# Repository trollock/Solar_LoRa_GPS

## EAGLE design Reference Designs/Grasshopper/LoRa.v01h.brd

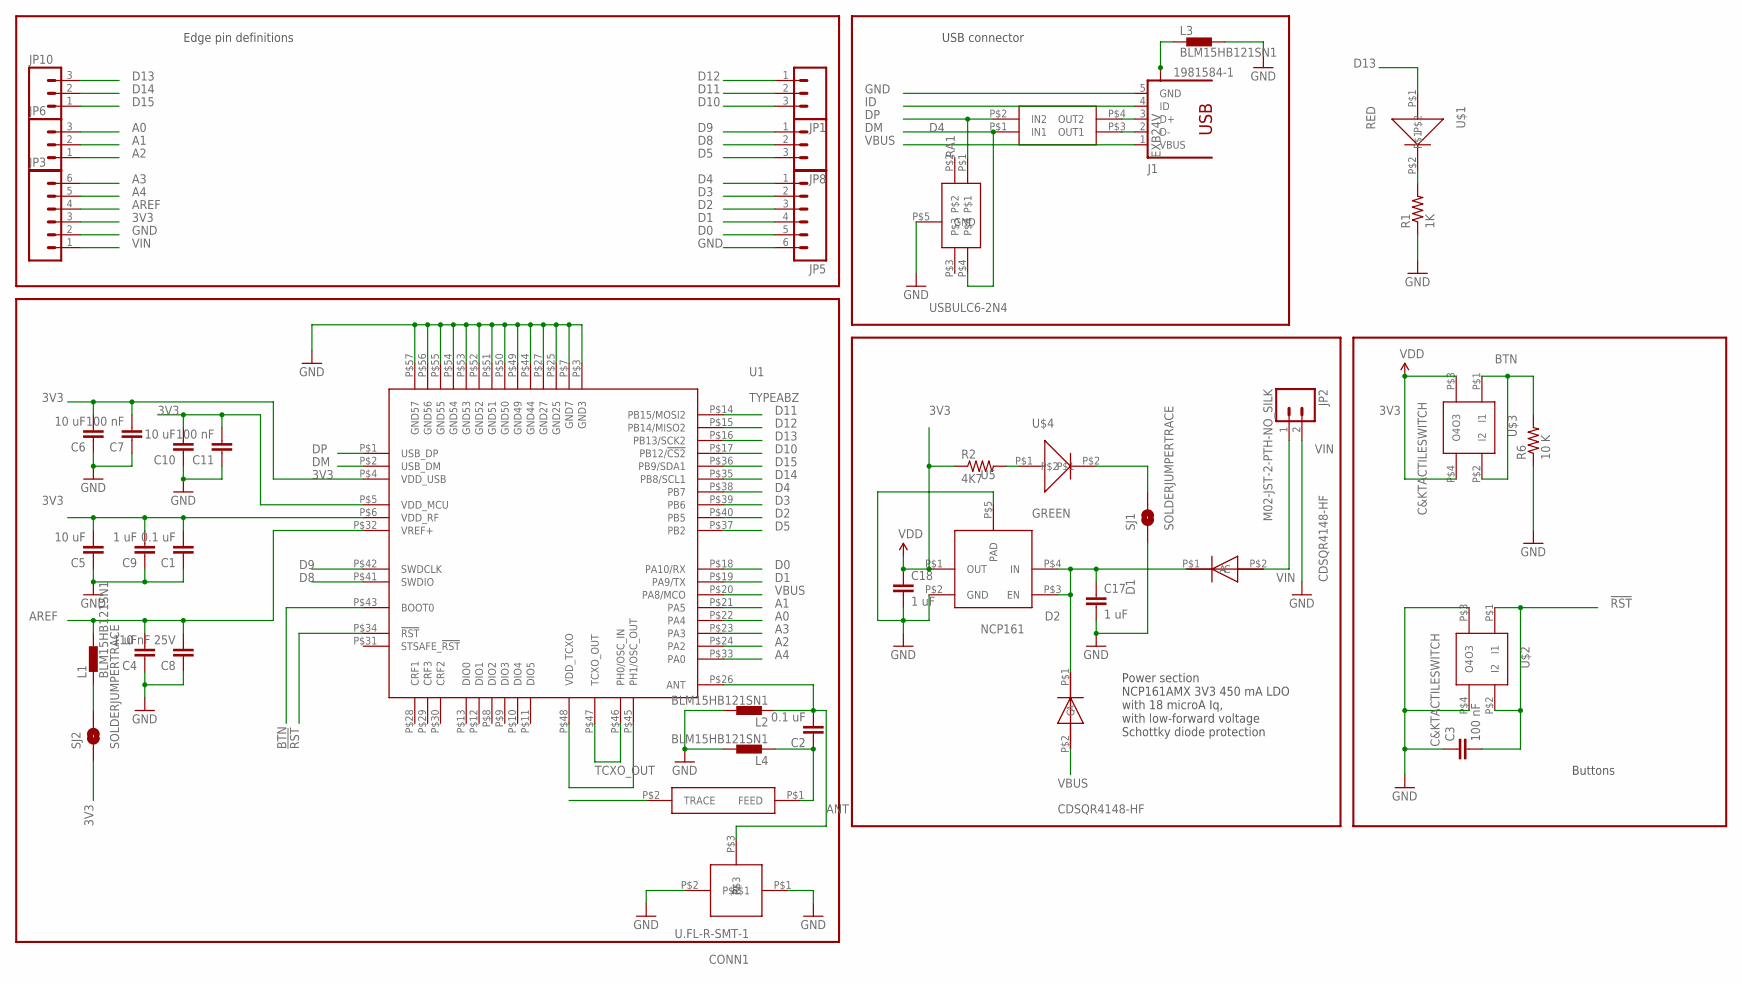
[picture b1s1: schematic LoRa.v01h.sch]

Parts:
C1, C2: 0.1 uF; 0402-CAP
C3, C7, C11: 100 nF; 0402-CAP
C4, C9, C17, C18: 1 uF; 0402-CAP
C5, C6, C10: 10 uF; 0402-CAP
C8: 10 nF 25V; 0402-CAP
CONN1: U.FL-R-SMT-1
D1, D2: CDSQR4148-HF
D4: USBULC6-2N4
J1: 1981584-1; MPN ZX62-AB-5PA(11)
JP1, JP6, JP8, JP10: M031X03_NO_SILK; 1X03_NO_SILK
JP2: M02-JST-2-PTH-NO_SILK; JST-2-PTH-NS
JP3, JP5: M06NO_SILK; 1X06_NO_SILK
L1, L2, L3, L4: BLM15HB121SN1; 0402
R1: 1K; 0402-RES
R2: 4K7; 0402-RES
R6: 10 K; 0402-RES
RA1: EXB24V
SJ1, SJ2: SOLDERJUMPERTRACE; SJ_2S-TRACE
U1: TYPEABZ
U5: NCP161
U$1: RED; 0402LED
U$2, U$3: C&KTACTILESWITCH
U$4: GREEN; 0402LED
U$5: JOHANSON0900AT43A0070

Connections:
3V3: C1.2, C5.2, C6.2, C7.2, C9.2, C10.2, C11.2, C18.1, JP3.3, R2.1, SJ2.1, U1.P$4 (VDD_USB), U1.P$5 (VDD_MCU), U1.P$6 (VDD_RF), U5.P$1 (OUT), U$3.P$3 (O3), U$3.P$4 (O4)
!RST: C3.2, U1.P$34 (!RST), U$2.P$1 (I1), U$2.P$2 (I2)
A0: JP6.3, U1.P$22 (PA4)
A1: JP6.2, U1.P$21 (PA5)
A2: JP6.1, U1.P$24 (PA2)
A3: JP3.6, U1.P$23 (PA3)
A4: JP3.5, U1.P$33 (PA0)
ANT: C2.1, L4.1, U$5.P$1 (FEED)
AREF: C4.2, C8.2, JP3.4, L1.2, U1.P$32 (VREF+)
BTN: R6.2, U1.P$43 (BOOT0), U$3.P$1 (I1), U$3.P$2 (I2)
D0: JP5.5, U1.P$18 (PA10/RX)
D1: JP5.4, U1.P$19 (PA9/TX)
D2: JP5.3, U1.P$40 (PB5)
D3: JP5.2, U1.P$39 (PB6)
D4: JP5.1, U1.P$38 (PB7)
D5: JP8.3, U1.P$37 (PB2)
D8: JP8.2, U1.P$41 (SWDIO)
D9: JP8.1, U1.P$42 (SWDCLK)
D10: JP1.3, U1.P$17 (PB12/!CS2)
D11: JP1.2, U1.P$14 (PB15/MOSI2)
D12: JP1.1, U1.P$15 (PB14/MISO2)
D13: JP10.3, U1.P$16 (PB13/SCK2), U$1.P$1
D14: JP10.2, U1.P$35 (PB8/SCL1)
D15: JP10.1, U1.P$36 (PB9/SDA1)
DM: D4.P$4, RA1.P$1 (IN1), U1.P$2 (USB_DM)
DP: D4.P$1, RA1.P$2 (IN2), U1.P$1 (USB_DP)
GND: C1.1, C3.1, C4.1, C5.1, C6.1, C7.1, C8.1, C9.1, C10.1, C11.1, C17.2, C18.2, CONN1.P$1, CONN1.P$2, D4.P$5 (GND), J1.5 (GND), JP2.2, JP3.2, JP5.6, L2.2, L3.2, L4.2, R1.1, R6.1, SJ1.1, U1.P$3 (GND3), U1.P$7 (GND7), U1.P$25 (GND25), U1.P$27 (GND27), U1.P$44 (GND44), U1.P$49 (GND49), U1.P$50 (GND50), U1.P$51 (GND51), U1.P$52 (GND52), U1.P$53 (GND53), U1.P$54 (GND54), U1.P$55 (GND55), U1.P$56 (GND56), U1.P$57 (GND57), U5.P$2 (GND), U5.P$5 (PAD), U$2.P$3 (O3), U$2.P$4 (O4)
ID: J1.4 (ID)
unnamed: R1.2, U$1.P$2
unnamed: L1.1, SJ2.2
unnamed: U1.P$45 (PH1/OSC_OUT), U1.P$48 (VDD_TCXO)
unnamed: SJ1.2, U$4.P$2
unnamed: J1.3 (D+), RA1.P$4 (OUT2)
unnamed: C2.2, CONN1.P$3, L2.1, U1.P$26 (ANT)
unnamed: J1.2 (D-), RA1.P$3 (OUT1)
unnamed: R2.2, U$4.P$1
unnamed: C17.1, D1.P$1 (C), D2.P$1 (C), U5.P$3 (EN), U5.P$4 (IN)
TCXO_OUT: U1.P$46 (PH0/OSC_IN), U1.P$47 (TCXO_OUT)
USB_SHIELD: J1.S1, J1.S2, J1.S3, J1.S4, L3.1
VBUS: D2.P$2 (A), J1.1 (VBUS), U1.P$20 (PA8/MCO)
VIN: D1.P$2 (A), JP2.1, JP3.1

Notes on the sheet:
Edge pin definitions
USB connector
Power section NCP161AMX 3V3 450 mA LDO with 18 microA Iq, with low-forward voltage Schottky diode protection
Buttons

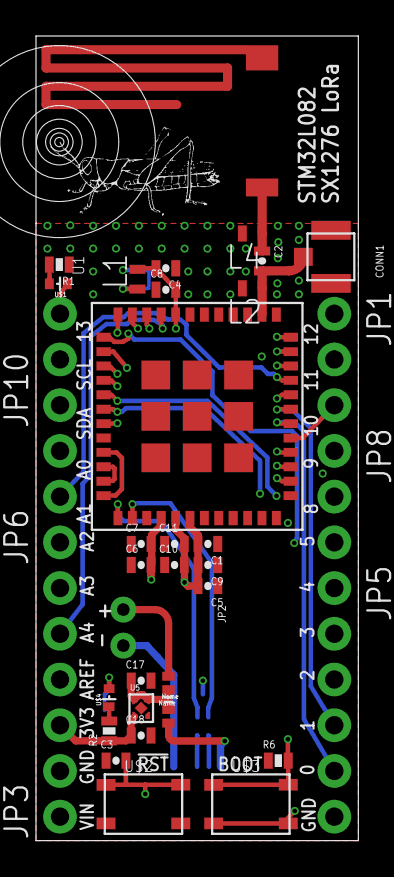
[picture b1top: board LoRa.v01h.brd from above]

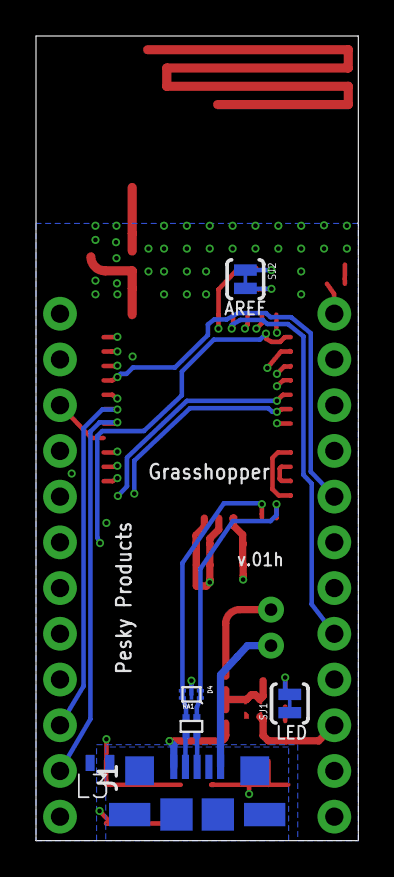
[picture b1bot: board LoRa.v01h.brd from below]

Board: 4 copper layers, 17.9 x 44.7 mm, 43 parts (6 on the bottom side), 40 nets.

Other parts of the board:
U$6: GRASSHOPPER

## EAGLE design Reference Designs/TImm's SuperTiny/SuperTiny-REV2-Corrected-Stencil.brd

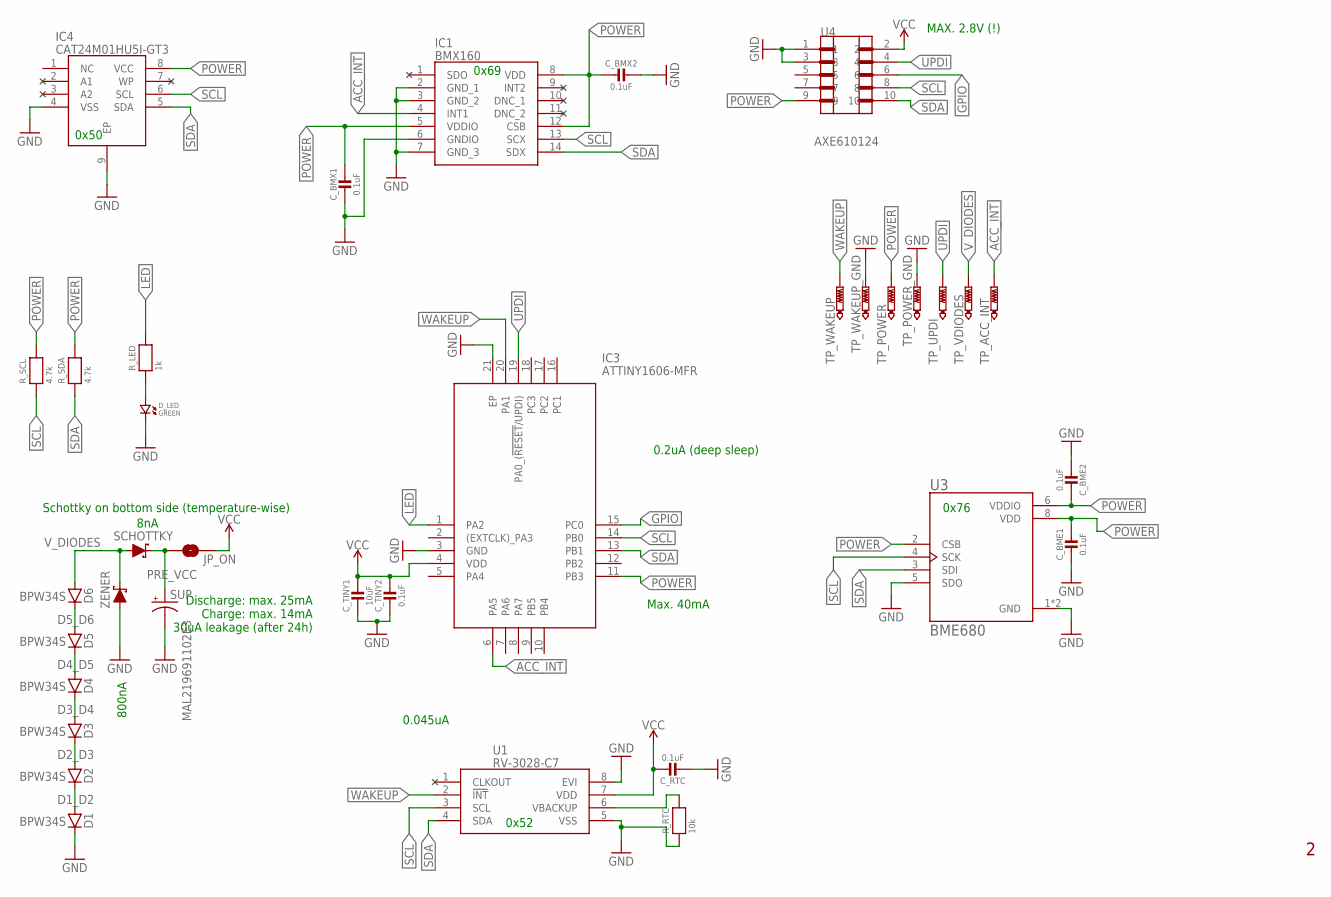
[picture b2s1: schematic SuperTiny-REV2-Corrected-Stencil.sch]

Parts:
C_BME1, C_BME2: 0.1uF; MICROBUILDER__0402MP
C_BMX1, C_BMX2: 0.1uF; MICROBUILDER__0402MP
C_RTC: 0.1uF; MICROBUILDER__0402MP
C_TINY1: 10uF; MICROBUILDER__0402MP
C_TINY2: 0.1uF; MICROBUILDER__0402MP
D1, D2, D3, D4, D5, D6: BPW34S
D_LED: GREEN; CMONR_STANDARDPARTS_0402.LED
IC1: BMX160; PQFN50P300X250X88-14N
IC3: ATTINY1606-MFR; QFN40P300X300X90-21N
IC4: CAT24M01HU5I-GT3; SON50P300X200X55-9N
JP_ON: JUMPER-SMT_2_NO_NO-SILK; SMT-JUMPER_2_NO_NO-SILK
R_LED: 1k; MICROBUILDER__0402MP
R_RTC: 10k; MICROBUILDER__0402MP
R_SCL: 4.7k; MICROBUILDER__0402MP
R_SDA: 4.7k; MICROBUILDER__0402MP
SCHOTTKY: NSR0140P2T5G
SUP: MAL219691102E3
TP_ACC_INT: PTR1TP06SQ; TP06SQ
TP_POWER: PTR1TP06SQ; TP06SQ
TP_POWER_GND: PTR1TP06SQ; TP06SQ
TP_UPDI: PTR1TP06SQ; TP06SQ
TP_VDIODES: PTR1TP06SQ; TP06SQ
TP_WAKEUP: PTR1TP06SQ; TP06SQ
TP_WAKEUP_GND: PTR1TP06SQ; TP06SQ
U1: RV-3028-C7; RV3028C7
U3: BME680; PSON80P300X300X100-8N
U4: AXE610124
ZENER: MMSZ4683T1G

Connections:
ACC_INT: IC1.4 (INT1), IC3.6 (PA5), TP_ACC_INT.TP
D1_D2: D1.PLUS, D2.MINUS
D2_D3: D2.PLUS, D3.MINUS
D3_D4: D3.PLUS, D4.MINUS
D4_D5: D4.PLUS, D5.MINUS
D5_D6: D5.PLUS, D6.MINUS
GND: C_BME1.2, C_BME2.2, C_BMX1.2, C_BMX2.1, C_RTC.2, C_TINY1.2, C_TINY2.2, D1.MINUS, D_LED.P$2 (2), IC1.2 (GND_1), IC1.3 (GND_2), IC1.6 (GNDIO), IC1.7 (GND_3), IC3.3 (GND), IC3.21 (EP), IC4.4 (VSS), IC4.9 (EP), R_RTC.1, SUP.MINUS (-), TP_POWER_GND.TP, TP_WAKEUP_GND.TP, U1.5 (VSS), U1.8 (EVI), U3.1 (GND), U3.5 (SDO), U3.7 (GND), U4.1, U4.3, ZENER.P$1 (AN)
GPIO: IC3.15 (PC0), U4.6
LED: IC3.1 (PA2), R_LED.2
unnamed: R_RTC.2, U1.6 (VBACKUP)
unnamed: D_LED.P$1 (1), R_LED.1
POWER: C_BME1.1, C_BME2.1, C_BMX1.1, C_BMX2.2, IC1.5 (VDDIO), IC1.8 (VDD), IC1.12 (CSB), IC3.11 (PB3), IC4.8 (VCC), R_SCL.2, R_SDA.2, TP_POWER.TP, U3.2 (CSB), U3.6 (VDDIO), U3.8 (VDD), U4.9
PRE_VCC: JP_ON.1, SCHOTTKY.P$2 (CA), SUP.PLUS (+)
SCL: IC1.13 (SCX), IC3.14 (PB0), IC4.6 (SCL), R_SCL.1, U1.3 (SCL), U3.4 (SCK), U4.8
SDA: IC1.14 (SDX), IC3.13 (PB1), IC4.5 (SDA), R_SDA.1, U1.4 (SDA), U3.3 (SDI), U4.10
UPDI: IC3.19 (PA0_(!RESET!/UPDI)), TP_UPDI.TP, U4.4
VCC: C_RTC.1, C_TINY1.1, C_TINY2.1, IC3.4 (VDD), JP_ON.2, U1.7 (VDD), U4.2
V_DIODES: D6.PLUS, SCHOTTKY.P$1 (AN), TP_VDIODES.TP, ZENER.P$2 (CA)
WAKEUP: IC3.20 (PA1), TP_WAKEUP.TP, U1.2 (!INT)

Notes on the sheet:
Schottky on bottom side (temperature-wise)
MAX. 2.8V (!)
0.045uA
800nA
0x50
0x69
0x52
8nA
0x76
0.2uA (deep sleep)
Discharge: max. 25mA Charge: max. 14mA 30uA leakage (after 24h)
Max. 40mA

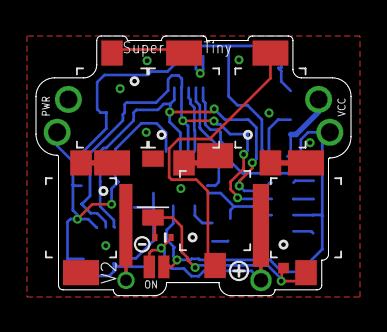
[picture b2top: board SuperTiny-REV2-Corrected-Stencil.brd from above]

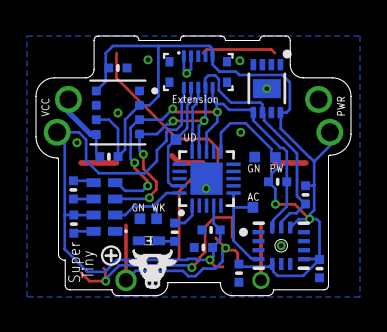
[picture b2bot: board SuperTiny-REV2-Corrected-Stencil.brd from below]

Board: 2 copper layers, 17.5 x 14.4 mm, 35 parts (24 on the bottom side), 19 nets.

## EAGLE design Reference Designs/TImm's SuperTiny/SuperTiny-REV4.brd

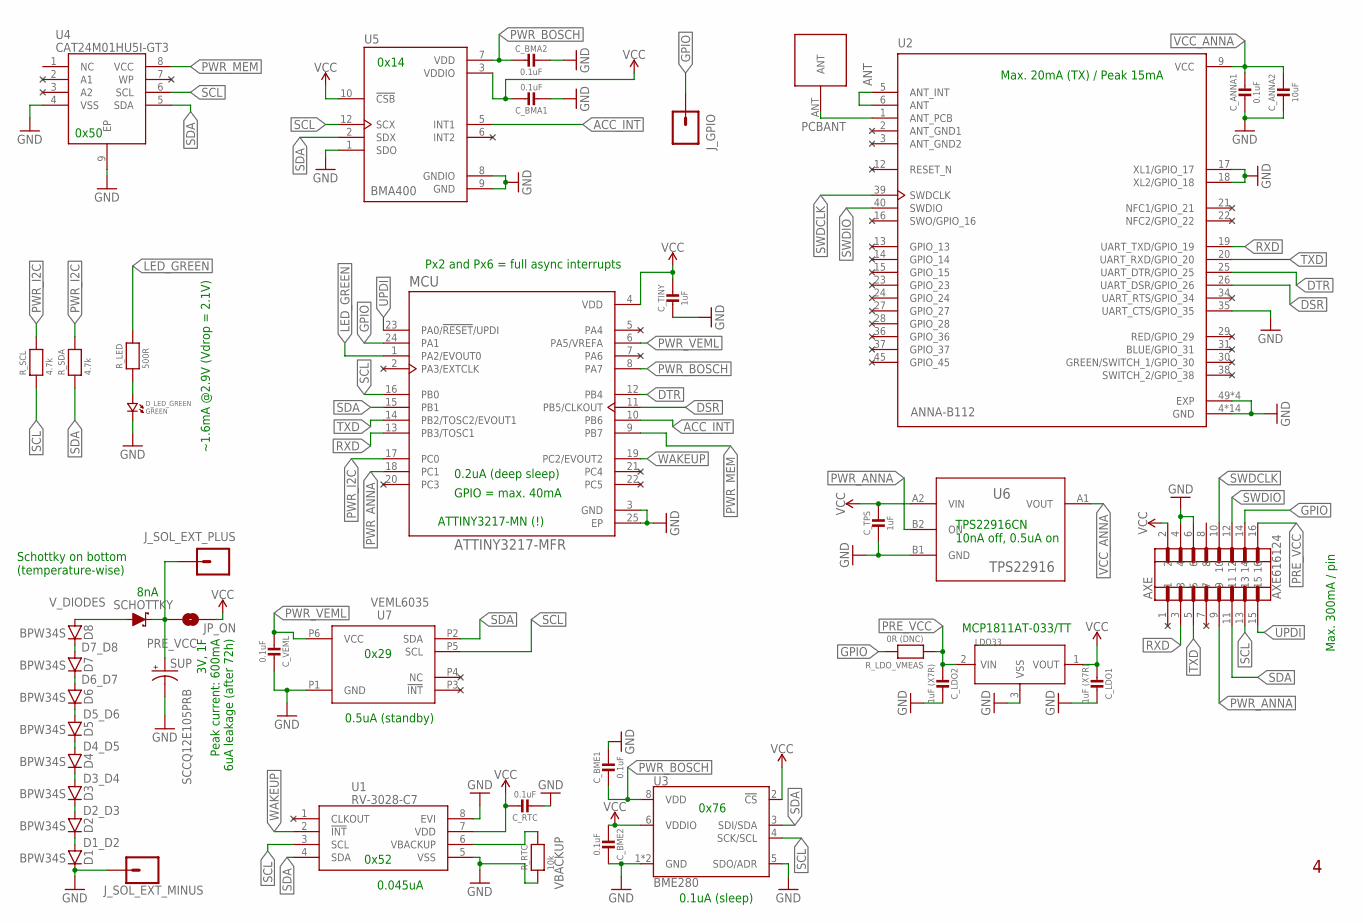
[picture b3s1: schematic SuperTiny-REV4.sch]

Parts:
AXE: AXE616124
C_ANNA1: 0.1uF; MICROBUILDER__0402MP
C_ANNA2: 10uF; MICROBUILDER__0402MP
C_BMA1, C_BMA2: 0.1uF; MICROBUILDER__0402MP
C_BME1, C_BME2: 0.1uF; MICROBUILDER__0402MP
C_LDO1, C_LDO2: 1uF (X7R); MICROBUILDER__0402MP
C_RTC: 0.1uF; MICROBUILDER__0402MP
C_TINY: 1uF; MICROBUILDER__0402MP
C_TPS: 1uF; MICROBUILDER__0402MP
C_VEML: 0.1uF; MICROBUILDER__0402MP
D1, D2, D3, D4, D5, D6, D7, D8: BPW34S
D_LED_GREEN: GREEN; CMONR_STANDARDPARTS_0402.LED
JP_ON: JUMPER-SMT_2_NO_NO-SILK; SMT-JUMPER_2_NO_NO-SILK
J_GPIO: CONN_01PTH_NO_SILK_SMALL; 1X01_SMALL
J_SOL_EXT_MINUS: CONN_01PTH_NO_SILK_SMALL; 1X01_SMALL
J_SOL_EXT_PLUS: CONN_01PTH_NO_SILK_SMALL; 1X01_SMALL
LDO33: MCP1812BT-018LB; SOT-23
MCU: ATTINY3217-MFR; QFN50P400X400X90-25N
R_LDO_VMEAS: 0R (DNC); MICROBUILDER__0402MP
R_LED: 500R; MICROBUILDER__0402MP
R_RTC: 10k; MICROBUILDER__0402MP
R_SCL: 4.7k; MICROBUILDER__0402MP
R_SDA: 4.7k; MICROBUILDER__0402MP
SCHOTTKY: NSR0140P2T5G
SUP: SCCQ12E105PRB
U1: RV-3028-C7; RV3028C7
U2: ANNA-B112; XCVR_ANNA-B112
U3: BME280; LGA-8-2.5X2.5
U4: CAT24M01HU5I-GT3; SON50P300X200X55-9N
U5: BMA400; XDCR_BMA400
U6: TPS22916
U7: VEML6035
U$4: ANNA-B112-PCB-ANTENNA

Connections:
ACC_INT: MCU.10 (PB6), U5.5 (INT1)
ANT: U2.5 (ANT_INT), U2.6 (ANT)
ANT_GND1: U2.2 (ANT_GND1)
ANT_GND2: U2.3 (ANT_GND2)
D1_D2: D1.PLUS, D2.MINUS
D2_D3: D2.PLUS, D3.MINUS
D3_D4: D3.PLUS, D4.MINUS
D4_D5: D4.PLUS, D5.MINUS
D5_D6: D5.PLUS, D6.MINUS
D6_D7: D6.PLUS, D7.MINUS
D7_D8: D7.PLUS, D8.MINUS
DSR: MCU.11 (PB5/CLKOUT), U2.26 (UART_DSR/GPIO_26)
DTR: MCU.12 (PB4), U2.25 (UART_DTR/GPIO_25)
GND: AXE.4, AXE.6, C_ANNA1.2, C_ANNA2.2, C_BMA1.2, C_BMA2.1, C_BME1.1, C_BME2.1, C_LDO1.1, C_LDO2.1, C_RTC.2, C_TINY.2, C_TPS.2, C_VEML.1, D1.MINUS, D_LED_GREEN.P$2 (2), J_SOL_EXT_MINUS.P$1, LDO33.3 (VSS), MCU.3 (GND), MCU.25 (EP), R_RTC.1, SUP.MINUS (-), U1.5 (VSS), U1.8 (EVI), U2.4 (GND), U2.7 (GND), U2.8 (GND), U2.10 (GND), U2.11 (GND), U2.17 (XL1/GPIO_17), U2.18 (XL2/GPIO_18), U2.32 (GND), U2.33 (GND), U2.35 (UART_CTS/GPIO_35), U2.41 (GND), U2.42 (GND), U2.43 (GND), U2.44 (GND), U2.46 (GND), U2.47 (GND), U2.48 (GND), U2.49 (EXP), U2.50 (EXP), U2.51 (EXP), U2.52 (EXP), U3.1 (GND), U3.5 (SDO/ADR), U3.7 (GND), U4.4 (VSS), U4.9 (EP), U5.1 (SDO), U5.8 (GNDIO), U5.9 (GND), U6.B1 (GND), U7.P1 (GND)
GPIO: AXE.14, J_GPIO.P$1, MCU.24 (PA1), R_LDO_VMEAS.2
LED_GREEN: MCU.1 (PA2/EVOUT0), R_LED.2
unnamed: D_LED_GREEN.P$1 (1), R_LED.1
PCBANT: U2.1 (ANT_PCB), U$4.ANT
PRE_VCC: AXE.16, C_LDO2.2, JP_ON.1, J_SOL_EXT_PLUS.P$1, LDO33.2 (VIN), R_LDO_VMEAS.1, SCHOTTKY.P$2 (CA), SUP.PLUS (+)
PWR_ANNA: AXE.9, MCU.18 (PC1), U6.B2 (ON)
PWR_BOSCH: C_BMA2.2, C_BME1.2, MCU.8 (PA7), U3.8 (VDD), U5.7 (VDD)
PWR_I2C: MCU.17 (PC0), R_SCL.2, R_SDA.2
PWR_MEM: MCU.9 (PB7), U4.8 (VCC)
PWR_VEML: C_VEML.2, MCU.6 (PA5/VREFA), U7.P6 (VCC)
RXD: AXE.3, MCU.13 (PB3/TOSC1), U2.19 (UART_TXD/GPIO_19)
SCL: AXE.13, MCU.16 (PB0), R_SCL.1, U1.3 (SCL), U3.4 (SCK/SCL), U4.6 (SCL), U5.12 (SCX), U7.P5 (SCL)
SDA: AXE.11, MCU.15 (PB1), R_SDA.1, U1.4 (SDA), U3.3 (SDI/SDA), U4.5 (SDA), U5.2 (SDX), U7.P2 (SDA)
SWDCLK: AXE.10, U2.39 (SWDCLK)
SWDIO: AXE.12, U2.40 (SWDIO)
TXD: AXE.5, MCU.14 (PB2/TOSC2/EVOUT1), U2.20 (UART_RXD/GPIO_20)
UPDI: AXE.15, MCU.23 (PA0/!RESET!/UPDI)
VBACKUP: R_RTC.2, U1.6 (VBACKUP)
VCC: AXE.2, C_BMA1.1, C_BME2.2, C_LDO1.2, C_RTC.1, C_TINY.1, C_TPS.1, JP_ON.2, LDO33.1 (VOUT), MCU.4 (VDD), U1.7 (VDD), U3.2 (!CS), U3.6 (VDDIO), U5.3 (VDDIO), U5.10 (!CSB), U6.A2 (VIN)
VCC_ANNA: C_ANNA1.1, C_ANNA2.1, U2.9 (VCC), U6.A1 (VOUT)
V_DIODES: D8.PLUS, SCHOTTKY.P$1 (AN)
WAKEUP: MCU.19 (PC2/EVOUT2), U1.2 (!INT)

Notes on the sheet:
Schottky on bottom (temperature-wise)
0.045uA
0x50
0x52
8nA
3V, 1F Peak current: 600mA 6uA leakage (after 72h)
Max. 20mA (TX) / Peak 15mA
~1.6mA @2.9V (Vdrop = 2.1V)
0x14
Max. 300mA / pin
0x76
0.1uA (sleep)
0.2uA (deep sleep)
GPIO = max. 40mA
Px2 and Px6 = full async interrupts
0x29
0.5uA (standby)
MCP1811AT-033/TT
TPS22916CN 10nA off, 0.5uA on
ATTINY3217-MN (!)

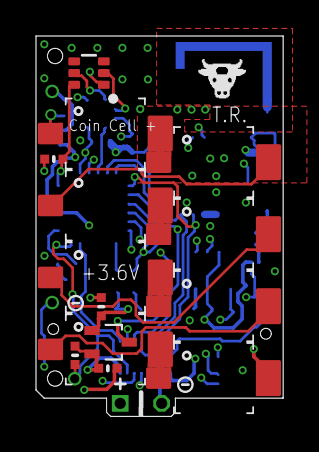
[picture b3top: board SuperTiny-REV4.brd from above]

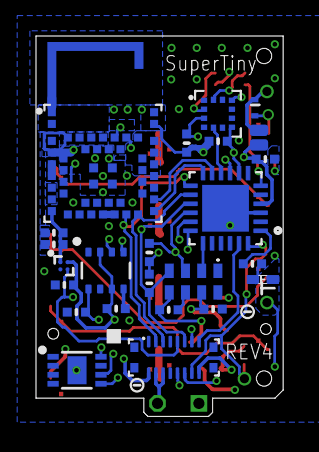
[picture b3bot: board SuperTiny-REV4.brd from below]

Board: 4 copper layers, 13.7 x 21.1 mm, 43 parts (25 on the bottom side), 34 nets.

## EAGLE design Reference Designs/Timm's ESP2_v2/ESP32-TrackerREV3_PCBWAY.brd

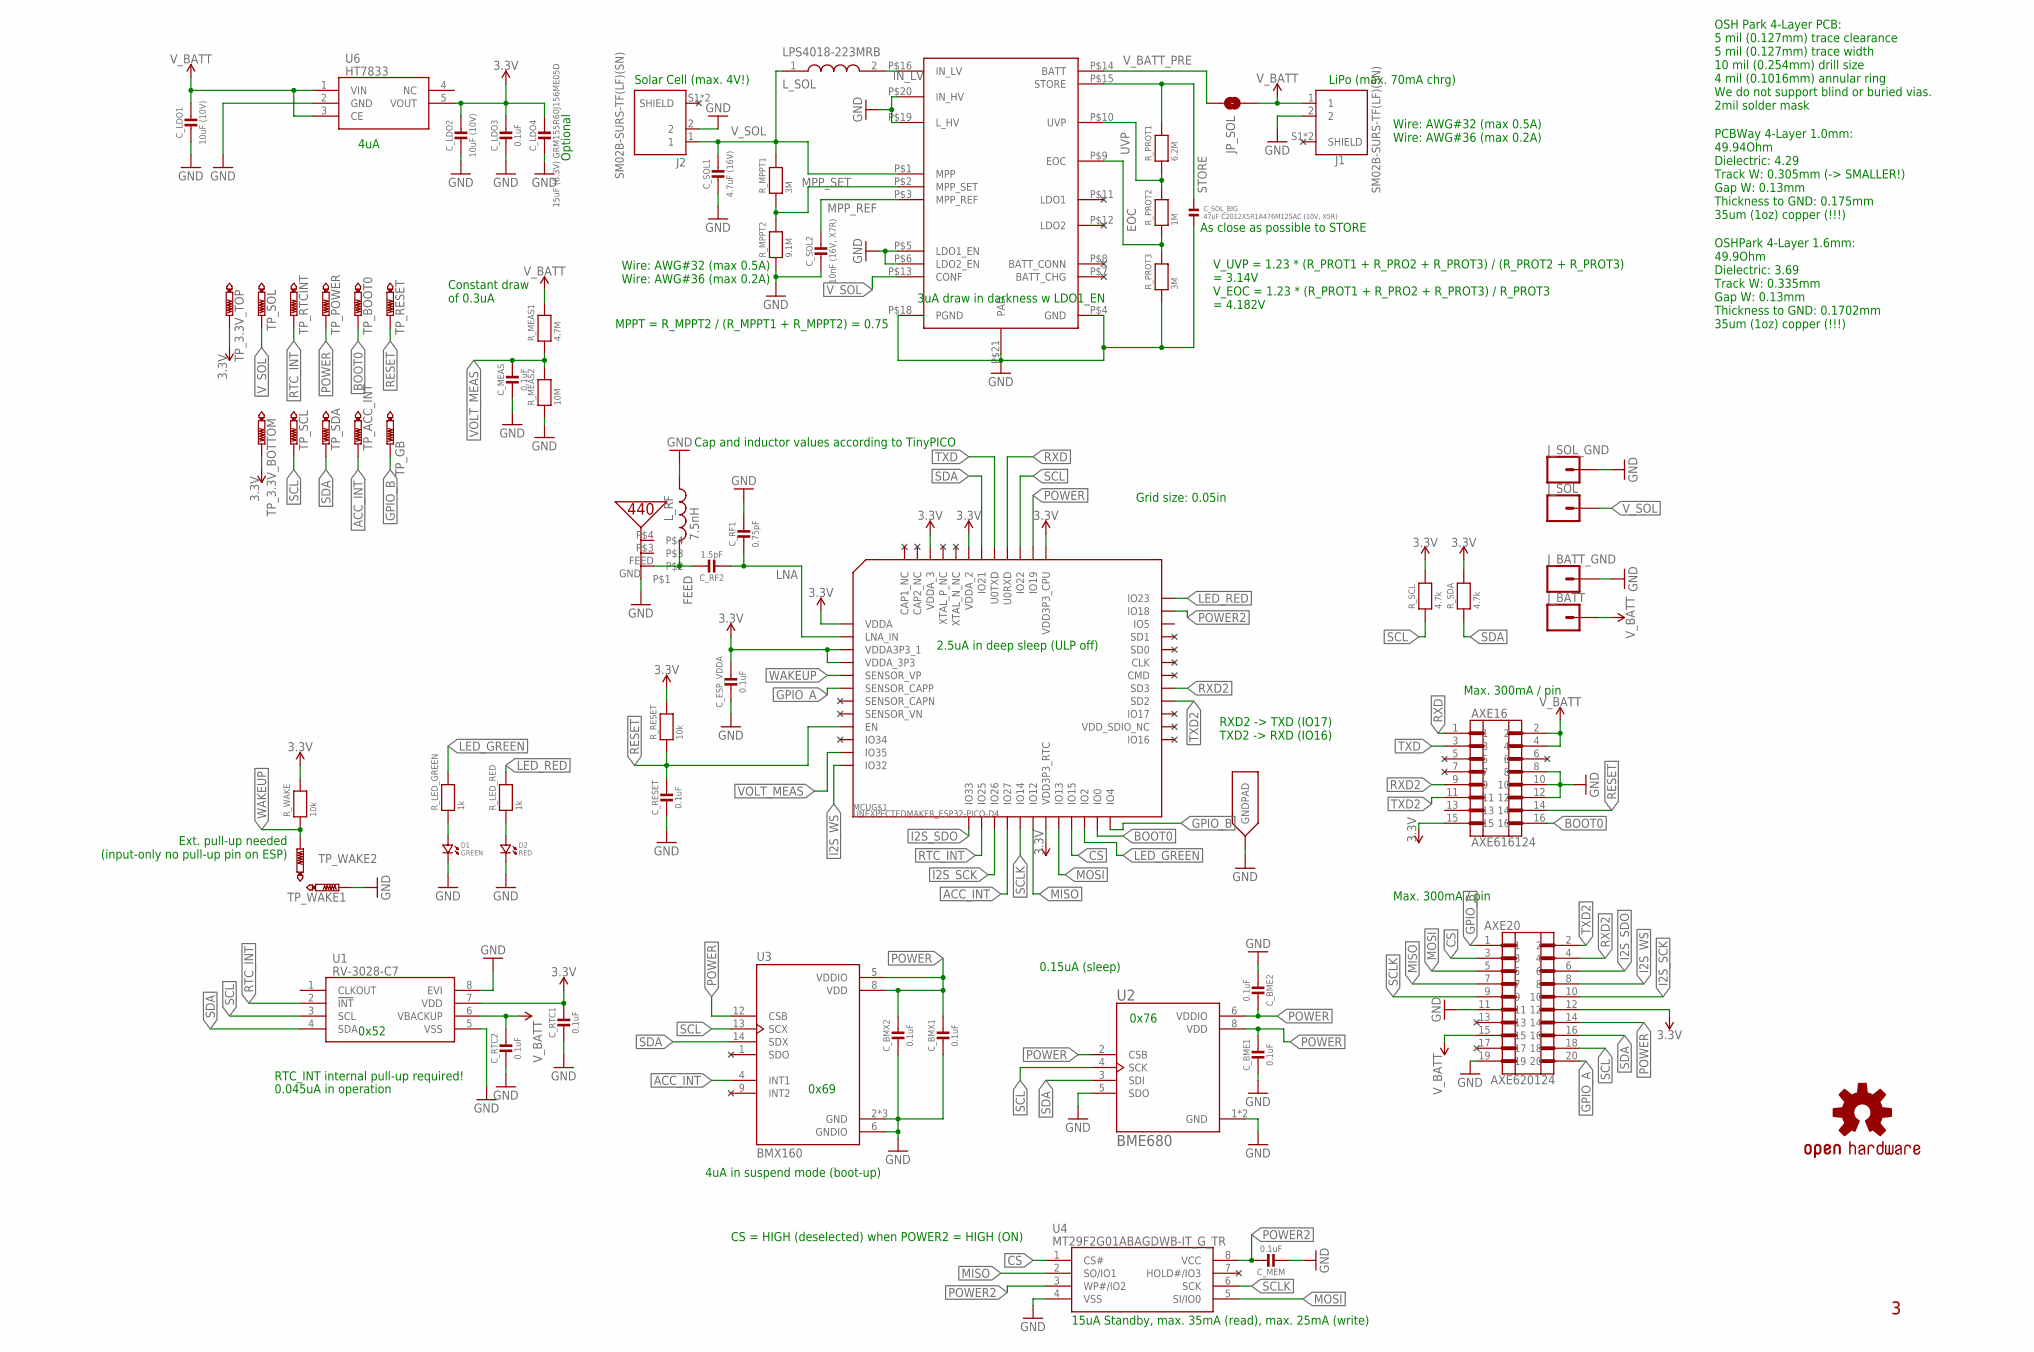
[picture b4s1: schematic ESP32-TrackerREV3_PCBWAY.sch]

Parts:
ANT: UNEXPECTEDMAKER_PRO-OB-440
AXE16: AXE616124
AXE20: AXE620124
C_BME1, C_BME2: 0.1uF; MICROBUILDER__0402MP
C_BMX1, C_BMX2: 0.1uF; MICROBUILDER__0402MP
C_ESP_VDDA: 0.1uF; MICROBUILDER__0402MP
C_LDO1, C_LDO2: 10uF (10V); MICROBUILDER__0402MP
C_LDO3: 0.1uF; MICROBUILDER__0402MP
C_LDO4: 15uF (6.3V) GRM155R60J156ME05D; MICROBUILDER__0402MP
C_MEAS: 0.1uF; MICROBUILDER__0402MP
C_MEM: 0.1uF; MICROBUILDER__0402MP
C_RESET: 0.1uF; MICROBUILDER__0402MP
C_RF1: 0.75pF; MICROBUILDER__0402MP
C_RF2: 1.5pF; MICROBUILDER__0402MP
C_RTC1, C_RTC2: 0.1uF; MICROBUILDER__0402MP
C_SOL1: 4.7uF (16V); MICROBUILDER__0402MP
C_SOL2: 10nF (16V, X7R); MICROBUILDER__0402MP
C_SOL_BIG: 47uF C2012X5R1A476M125AC (10V, X5R); 0805
D1: GREEN; CMONR_STANDARDPARTS_0402.LED
D2: RED; CMONR_STANDARDPARTS_0402.LED
J1, J2: SM02B-SURS-TF(LF)(SN); JST_SM02B-SURS-TF(LF)(SN)
JP_SOL: JUMPER-SMT_2_NO_NO-SILK; SMT-JUMPER_2_NO_NO-SILK
J_BATT: CONN_01PTH_NO_SILK_SMALL; 1X01_SMALL
J_BATT_GND: CONN_01PTH_NO_SILK_SMALL; 1X01_SMALL
J_SOL: CONN_01PTH_NO_SILK_SMALL; 1X01_SMALL
J_SOL_GND: CONN_01PTH_NO_SILK_SMALL; 1X01_SMALL
LOGO1: OSHW-LOGOS; OSHW-LOGO-S
L_RF: 7.5nH; NORDIC_NRF_RESC0402_N
L_SOL: LPS4018-223MRB; LPS4018
MCU: UNEXPECTEDMAKER_ESP32-PICO-D4; UNEXPECTEDMAKER_PICO-D4-QFN48
R_LED_GREEN: 1k; MICROBUILDER__0402MP
R_LED_RED: 1k; MICROBUILDER__0402MP
R_MEAS1: 4.7M; MICROBUILDER__0402MP
R_MEAS2: 10M; MICROBUILDER__0402MP
R_MPPT1: 3M; MICROBUILDER__0402MP
R_MPPT2: 9.1M; MICROBUILDER__0402MP
R_PROT1: 6.2M; MICROBUILDER__0402MP
R_PROT2: 1M; MICROBUILDER__0402MP
R_PROT3: 3M; MICROBUILDER__0402MP
R_RESET: 10k; MICROBUILDER__0402MP
R_SCL: 4.7k; MICROBUILDER__0402MP
R_SDA: 4.7k; MICROBUILDER__0402MP
R_WAKE: 10k; MICROBUILDER__0402MP
TP_3.3V_BOTTOM, TP_3.3V_TOP: PTR1TP06SQ; TP06SQ
TP_ACC_INT: PTR1TP06SQ; TP06SQ
TP_BOOT0: PTR1TP06SQ; TP06SQ
TP_GB: PTR1TP06SQ; TP06SQ
TP_POWER: PTR1TP06SQ; TP06SQ
TP_RESET: PTR1TP06SQ; TP06SQ
TP_RTCINT: PTR1TP06SQ; TP06SQ
TP_SCL: PTR1TP06SQ; TP06SQ
TP_SDA: PTR1TP06SQ; TP06SQ
TP_SOL: PTR1TP06SQ; TP06SQ
TP_WAKE1, TP_WAKE2: PTR1TP06SQ; TP06SQ
U1: RV-3028-C7; RV3028C7
U2: BME680; PSON80P300X300X100-8N
U3: BMX160; PQFN50P250X300X100-14N
U4: MT29F2G01ABAGDWB-IT_G_TR; SON127P800X600X65-8N
U5: SPV1050
U6: HT7833; SOT95P280X80-5N

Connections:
3.3V: AXE16.15, AXE20.12, C_ESP_VDDA.1, C_LDO2.1, C_LDO3.1, C_LDO4.1, C_RTC1.1, MCU.1 (VDDA), MCU.3 (VDDA3P3_1), MCU.4 (VDDA_3P3), MCU.19 (VDD3P3_RTC), MCU.37 (VDD3P3_CPU), MCU.43 (VDDA_2), MCU.46 (VDDA_3), R_RESET.2, R_SCL.2, R_SDA.2, R_WAKE.2, TP_3.3V_BOTTOM.TP, TP_3.3V_TOP.TP, U1.7 (VDD), U6.5 (VOUT)
ACC_INT: MCU.16 (IO27), TP_ACC_INT.TP, U3.4 (INT1)
BOOT0: AXE16.16, MCU.23 (IO0), TP_BOOT0.TP
CS: AXE20.3, MCU.21 (IO15), U4.1 (CS#)
EOC: R_PROT2.1, R_PROT3.2, U5.P$9 (EOC)
FEED: ANT.FEED, C_RF2.1, L_RF.2
GND: ANT.GND, AXE16.8, AXE16.10, AXE16.12, AXE20.11, AXE20.19, C_BME1.2, C_BME2.2, C_BMX1.2, C_BMX2.2, C_ESP_VDDA.2, C_LDO1.2, C_LDO2.2, C_LDO3.2, C_LDO4.2, C_MEAS.2, C_MEM.2, C_RESET.2, C_RF1.1, C_RTC1.2, C_RTC2.2, C_SOL1.2, C_SOL2.2, C_SOL_BIG.2, D1.P$2 (2), D2.P$2 (2), J1.2, J2.2, J_BATT_GND.P$1, J_SOL_GND.P$1, L_RF.1, MCU.EXP (GNDPAD), R_MEAS2.1, R_MPPT2.1, R_PROT3.1, TP_WAKE1.TP, U1.5 (VSS), U1.8 (EVI), U2.1 (GND), U2.5 (SDO), U2.7 (GND), U3.2 (GND), U3.3 (GND), U3.6 (GNDIO), U3.7 (GND), U4.4 (VSS), U5.P$4 (GND), U5.P$5 (LDO1_EN), U5.P$6 (LDO2_EN), U5.P$18 (PGND), U5.P$19 (L_HV), U5.P$20 (IN_HV), U5.P$21 (PAD), U6.2 (GND)
GPIO_A: AXE20.20, MCU.6 (SENSOR_CAPP)
GPIO_B: AXE20.1, MCU.24 (IO4), TP_GB.TP
I2S_SCK: AXE20.10, MCU.15 (IO26)
I2S_SDO: AXE20.6, MCU.13 (IO33)
I2S_WS: AXE20.8, MCU.12 (IO32)
IN_LV: L_SOL.2, U5.P$16 (IN_LV)
LED_GREEN: MCU.22 (IO2), R_LED_GREEN.2
LED_RED: MCU.36 (IO23), R_LED_RED.2
LNA: C_RF1.2, C_RF2.2, MCU.2 (LNA_IN)
MISO: AXE20.7, MCU.18 (IO12), U4.2 (SO/IO1)
MOSI: AXE20.5, MCU.20 (IO13), U4.5 (SI/IO0)
MPP_REF: C_SOL2.1, U5.P$3 (MPP_REF)
MPP_SET: R_MPPT1.1, R_MPPT2.2, U5.P$2 (MPP_SET)
unnamed: D1.P$1 (1), R_LED_GREEN.1
unnamed: D2.P$1 (1), R_LED_RED.1
POWER: AXE20.14, C_BME1.1, C_BME2.1, C_BMX1.1, C_BMX2.1, MCU.38 (IO19), TP_POWER.TP, U2.2 (CSB), U2.6 (VDDIO), U2.8 (VDD), U3.5 (VDDIO), U3.8 (VDD), U3.12 (CSB)
POWER2: C_MEM.1, MCU.35 (IO18), U4.3 (WP#/IO2), U4.8 (VCC)
RESET: AXE16.14, C_RESET.1, MCU.9 (EN), R_RESET.1, TP_RESET.TP
RTC_INT: MCU.14 (IO25), TP_RTCINT.TP, U1.2 (!INT)
RXD: AXE16.1, MCU.40 (U0RXD)
RXD2: AXE16.9, AXE20.4, MCU.29 (SD3)
SCL: AXE20.18, MCU.39 (IO22), R_SCL.1, TP_SCL.TP, U1.3 (SCL), U2.4 (SCK), U3.13 (SCX)
SCLK: AXE20.9, MCU.17 (IO14), U4.6 (SCK)
SDA: AXE20.16, MCU.42 (IO21), R_SDA.1, TP_SDA.TP, U1.4 (SDA), U2.3 (SDI), U3.14 (SDX)
SENSOR_CAPN: MCU.7 (SENSOR_CAPN)
STORE: C_SOL_BIG.1, R_PROT1.2, U5.P$15 (STORE)
TXD: AXE16.3, MCU.41 (U0TXD)
TXD2: AXE16.11, AXE20.2, MCU.28 (SD2)
UVP: R_PROT1.1, R_PROT2.2, U5.P$10 (UVP)
VOLT_MEAS: C_MEAS.1, MCU.11 (IO35), R_MEAS1.1, R_MEAS2.2
V_BATT: AXE16.2, AXE16.4, AXE20.15, C_LDO1.1, C_RTC2.1, J1.1, JP_SOL.2, J_BATT.P$1, R_MEAS1.2, U1.6 (VBACKUP), U6.1 (VIN), U6.3 (CE)
V_BATT_PRE: JP_SOL.1, U5.P$14 (BATT)
V_SOL: C_SOL1.1, J2.1, J_SOL.P$1, L_SOL.1, R_MPPT1.2, TP_SOL.TP, U5.P$1 (MPP), U5.P$13 (CONF)
WAKEUP: MCU.5 (SENSOR_VP), R_WAKE.1, TP_WAKE2.TP

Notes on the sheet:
Cap and inductor values according to TinyPICO
Grid size: 0.05in
RXD2 -> TXD (IO17) TXD2 -> RXD (IO16)
RTC_INT internal pull-up required!
Constant draw of 0.3uA
As close as possible to STORE
Solar Cell (max. 4V!)
LiPo (max. 70mA chrg)
0.045uA in operation
4uA
2.5uA in deep sleep (ULP off)
OSH Park 4-Layer PCB: 5 mil (0.127mm) trace clearance 5 mil (0.127mm) trace width 10 mil (0.254mm) drill size 4 mil (0.1016mm) annular ring We do not support blind or buried vias. 2mil solder mask
0x76
Max. 300mA / pin
OSHPark 4-Layer 1.6mm: 49.9Ohm Dielectric: 3.69 Track W: 0.335mm Gap W: 0.13mm Thickness to GND: 0.1702mm 35um (1oz) copper (!!!)
0.15uA (sleep)
3uA draw in darkness w LDO1_EN
MPPT = R_MPPT2 / (R_MPPT1 + R_MPPT2) = 0.75
PCBWay 4-Layer 1.0mm: 49.94Ohm Dielectric: 4.29 Track W: 0.305mm (-> SMALLER!) Gap W: 0.13mm Thickness to GND: 0.175mm 35um (1oz) copper (!!!)
V_UVP = 1.23 * (R_PROT1 + R_PRO2 + R_PROT3) / (R_PROT2 + R_PROT3) = 3.14V V_EOC = 1.23 * (R_PROT1 + R_PRO2 + R_PROT3) / R_PROT3 = 4.182V
Optional
Ext. pull-up needed (input-only no pull-up pin on ESP)
4uA in suspend mode (boot-up)
Wire: AWG#32 (max 0.5A) Wire: AWG#36 (max 0.2A)
CS = HIGH (deselected) when POWER2 = HIGH (ON)
15uA Standby, max. 35mA (read), max. 25mA (write)
0x52
0x69

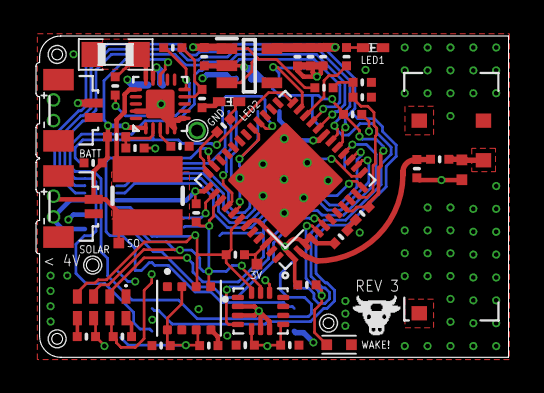
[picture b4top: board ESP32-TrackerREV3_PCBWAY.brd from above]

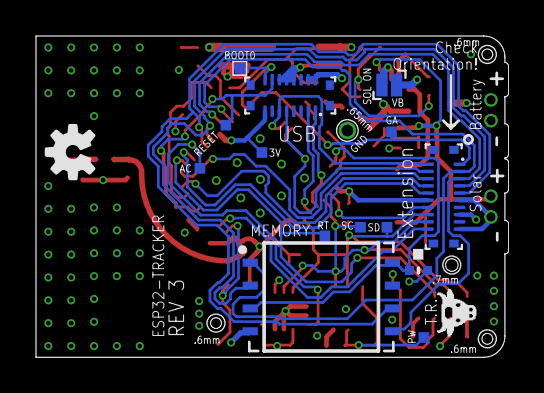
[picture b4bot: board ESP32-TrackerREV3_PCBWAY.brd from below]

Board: 4 copper layers, 26.2 x 17.9 mm, 67 parts (15 on the bottom side), 40 nets.

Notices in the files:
parts and their libraries:
SparkFun-Connectors: Licensing: Creative Commons ShareAlike 4.0 International - https://creativecommons.org/licenses/by-sa/4.0
con-usb: Copyright (C) 2008, Bob Starr
